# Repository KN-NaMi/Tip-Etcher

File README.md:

# 🧪 Tip Etcher for Scanning Tunneling Microscopy (STM) 🧪

**Overview**
This project is a **Tip Etcher** designed for the fabrication of fine tungsten tips required for **Scanning Tunneling Microscopy (STM)**. The inspiration for this project comes from the [Zyrus Tip Etcher](https://hackaday.io/project/191941-zyrus-tip-etcher-for-scanning-tunneling-microscopy) project, with modifications to improve performance and usability.

**✨ Proposed Changes ✨**
* Updated README.md
* Changed structure to vertical based desgin, using avaible aluminium profiles.
* Upgraded documentation in cad's folder
* Removed previous version's files in cad's folder

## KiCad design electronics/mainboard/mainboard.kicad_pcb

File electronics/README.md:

# PCB Design

This folder contains the PCB design files for the Tip Etcher.

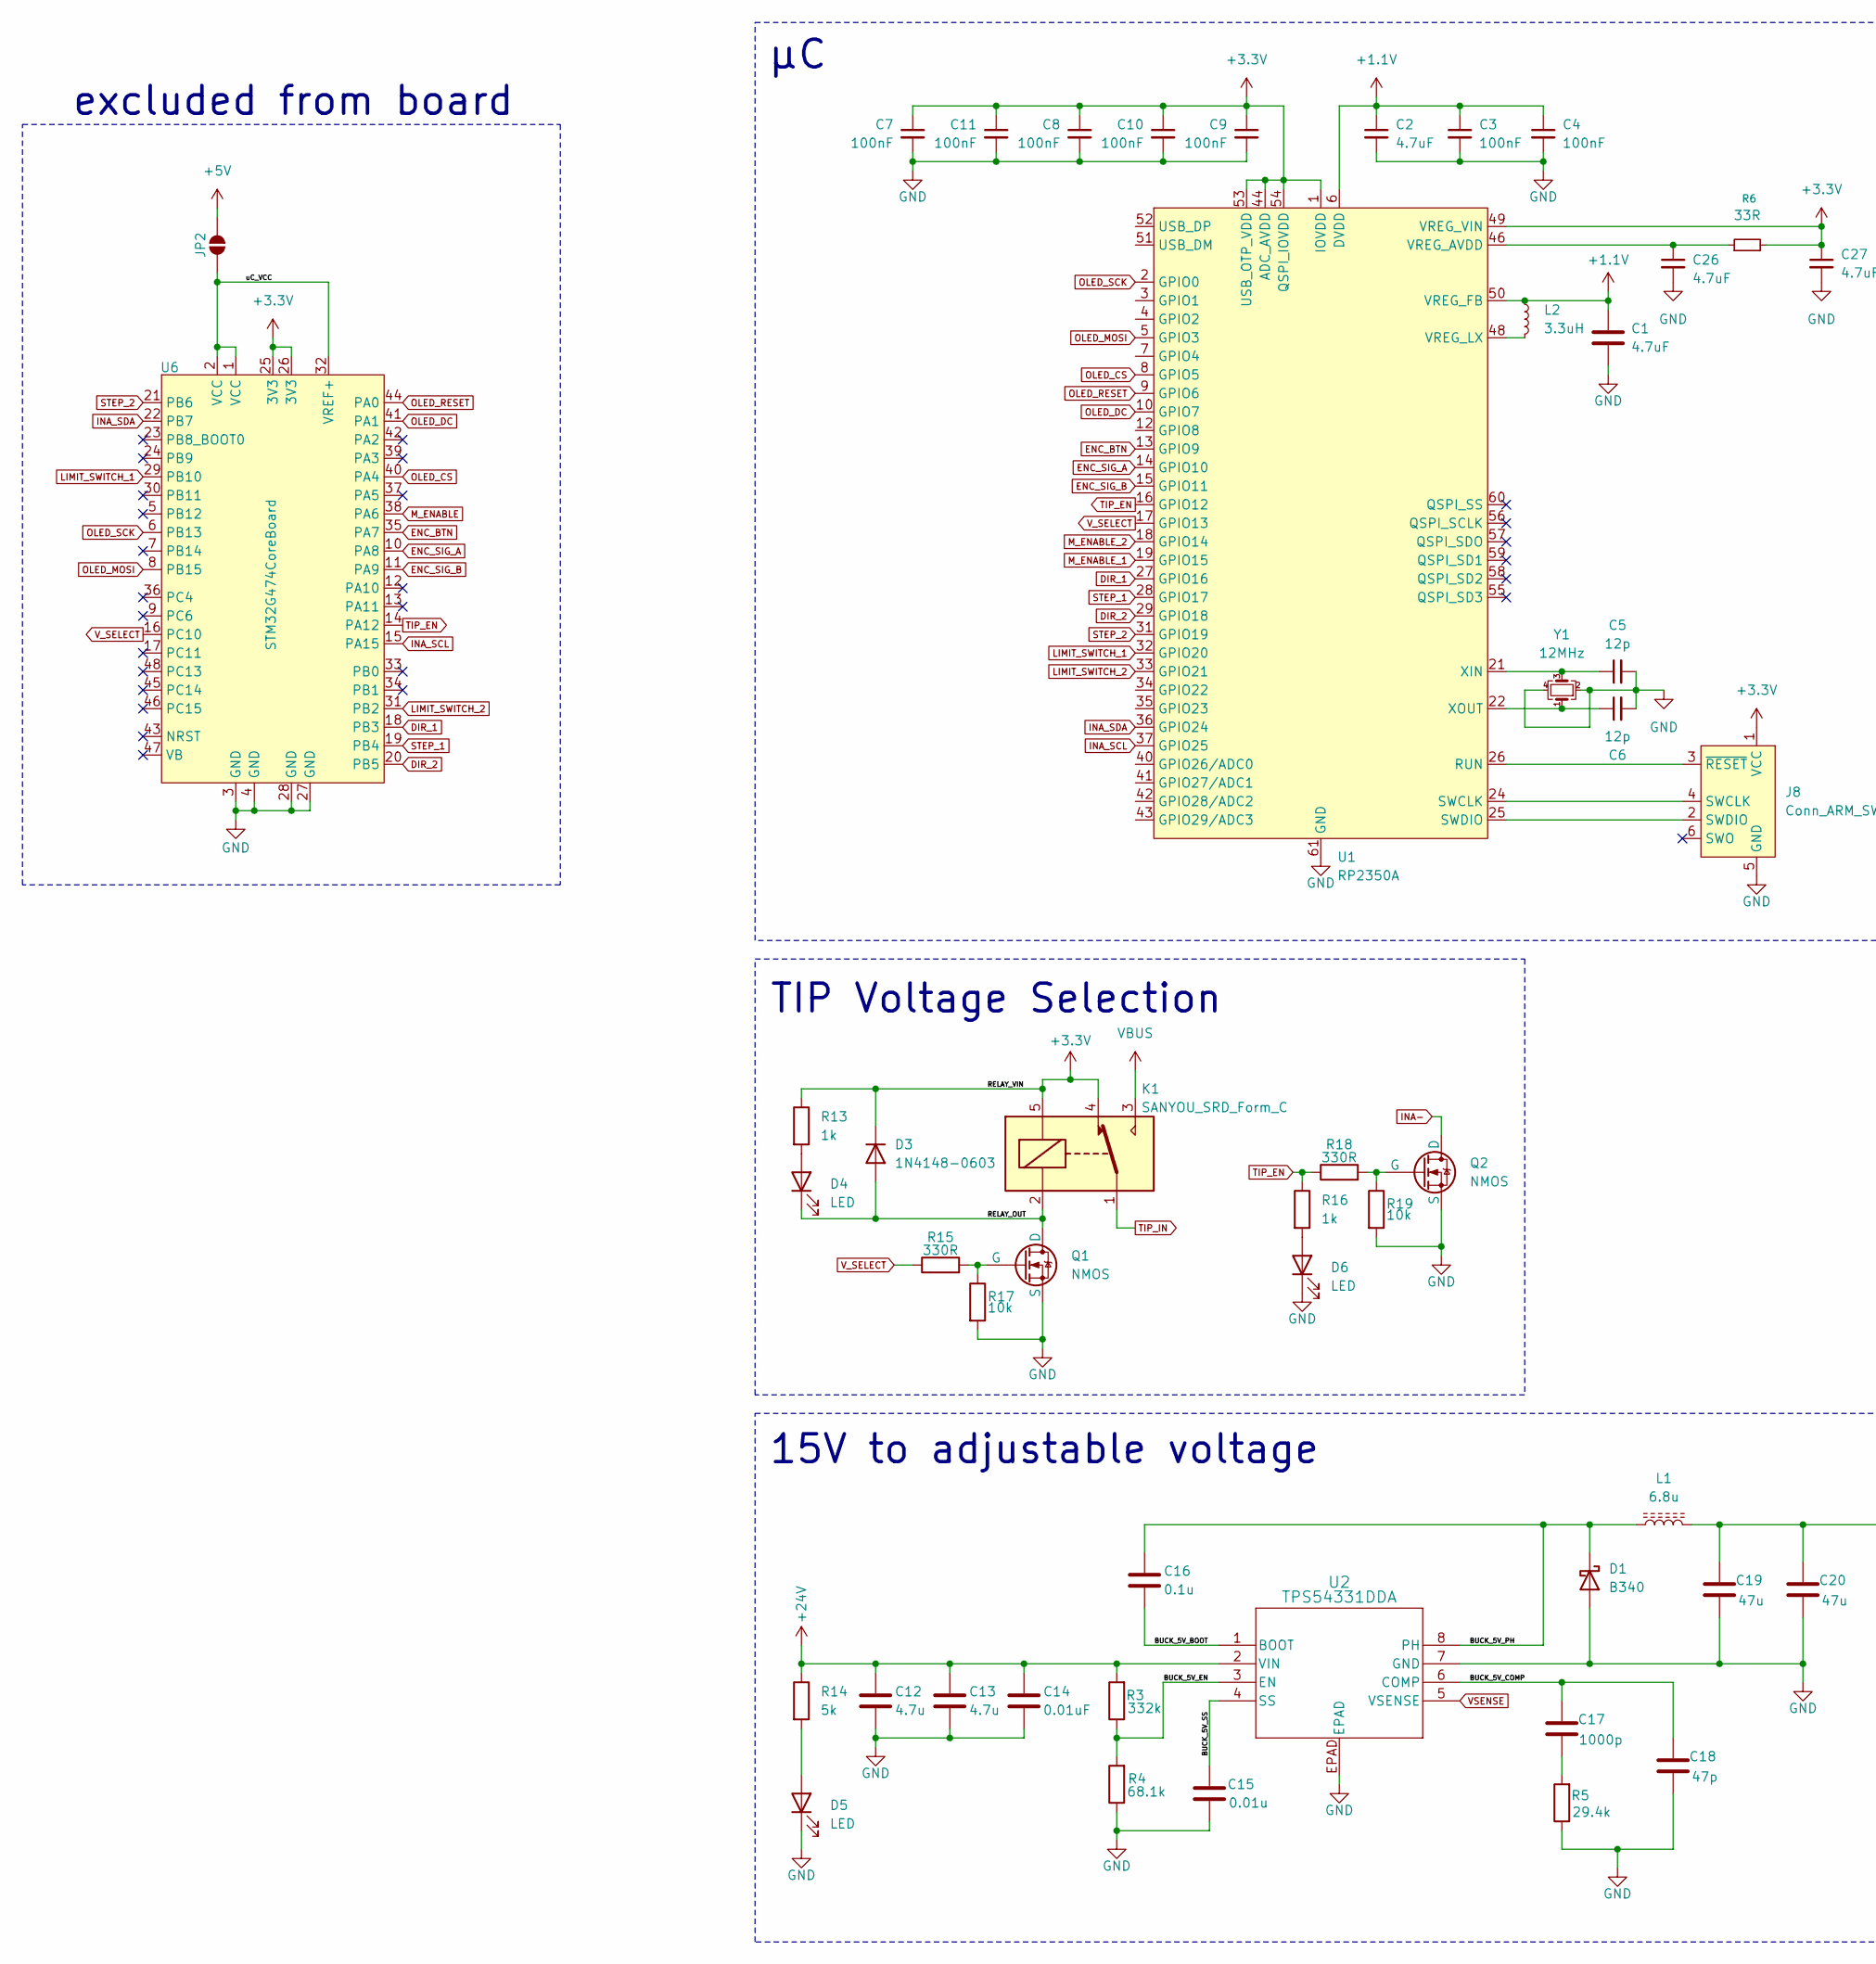
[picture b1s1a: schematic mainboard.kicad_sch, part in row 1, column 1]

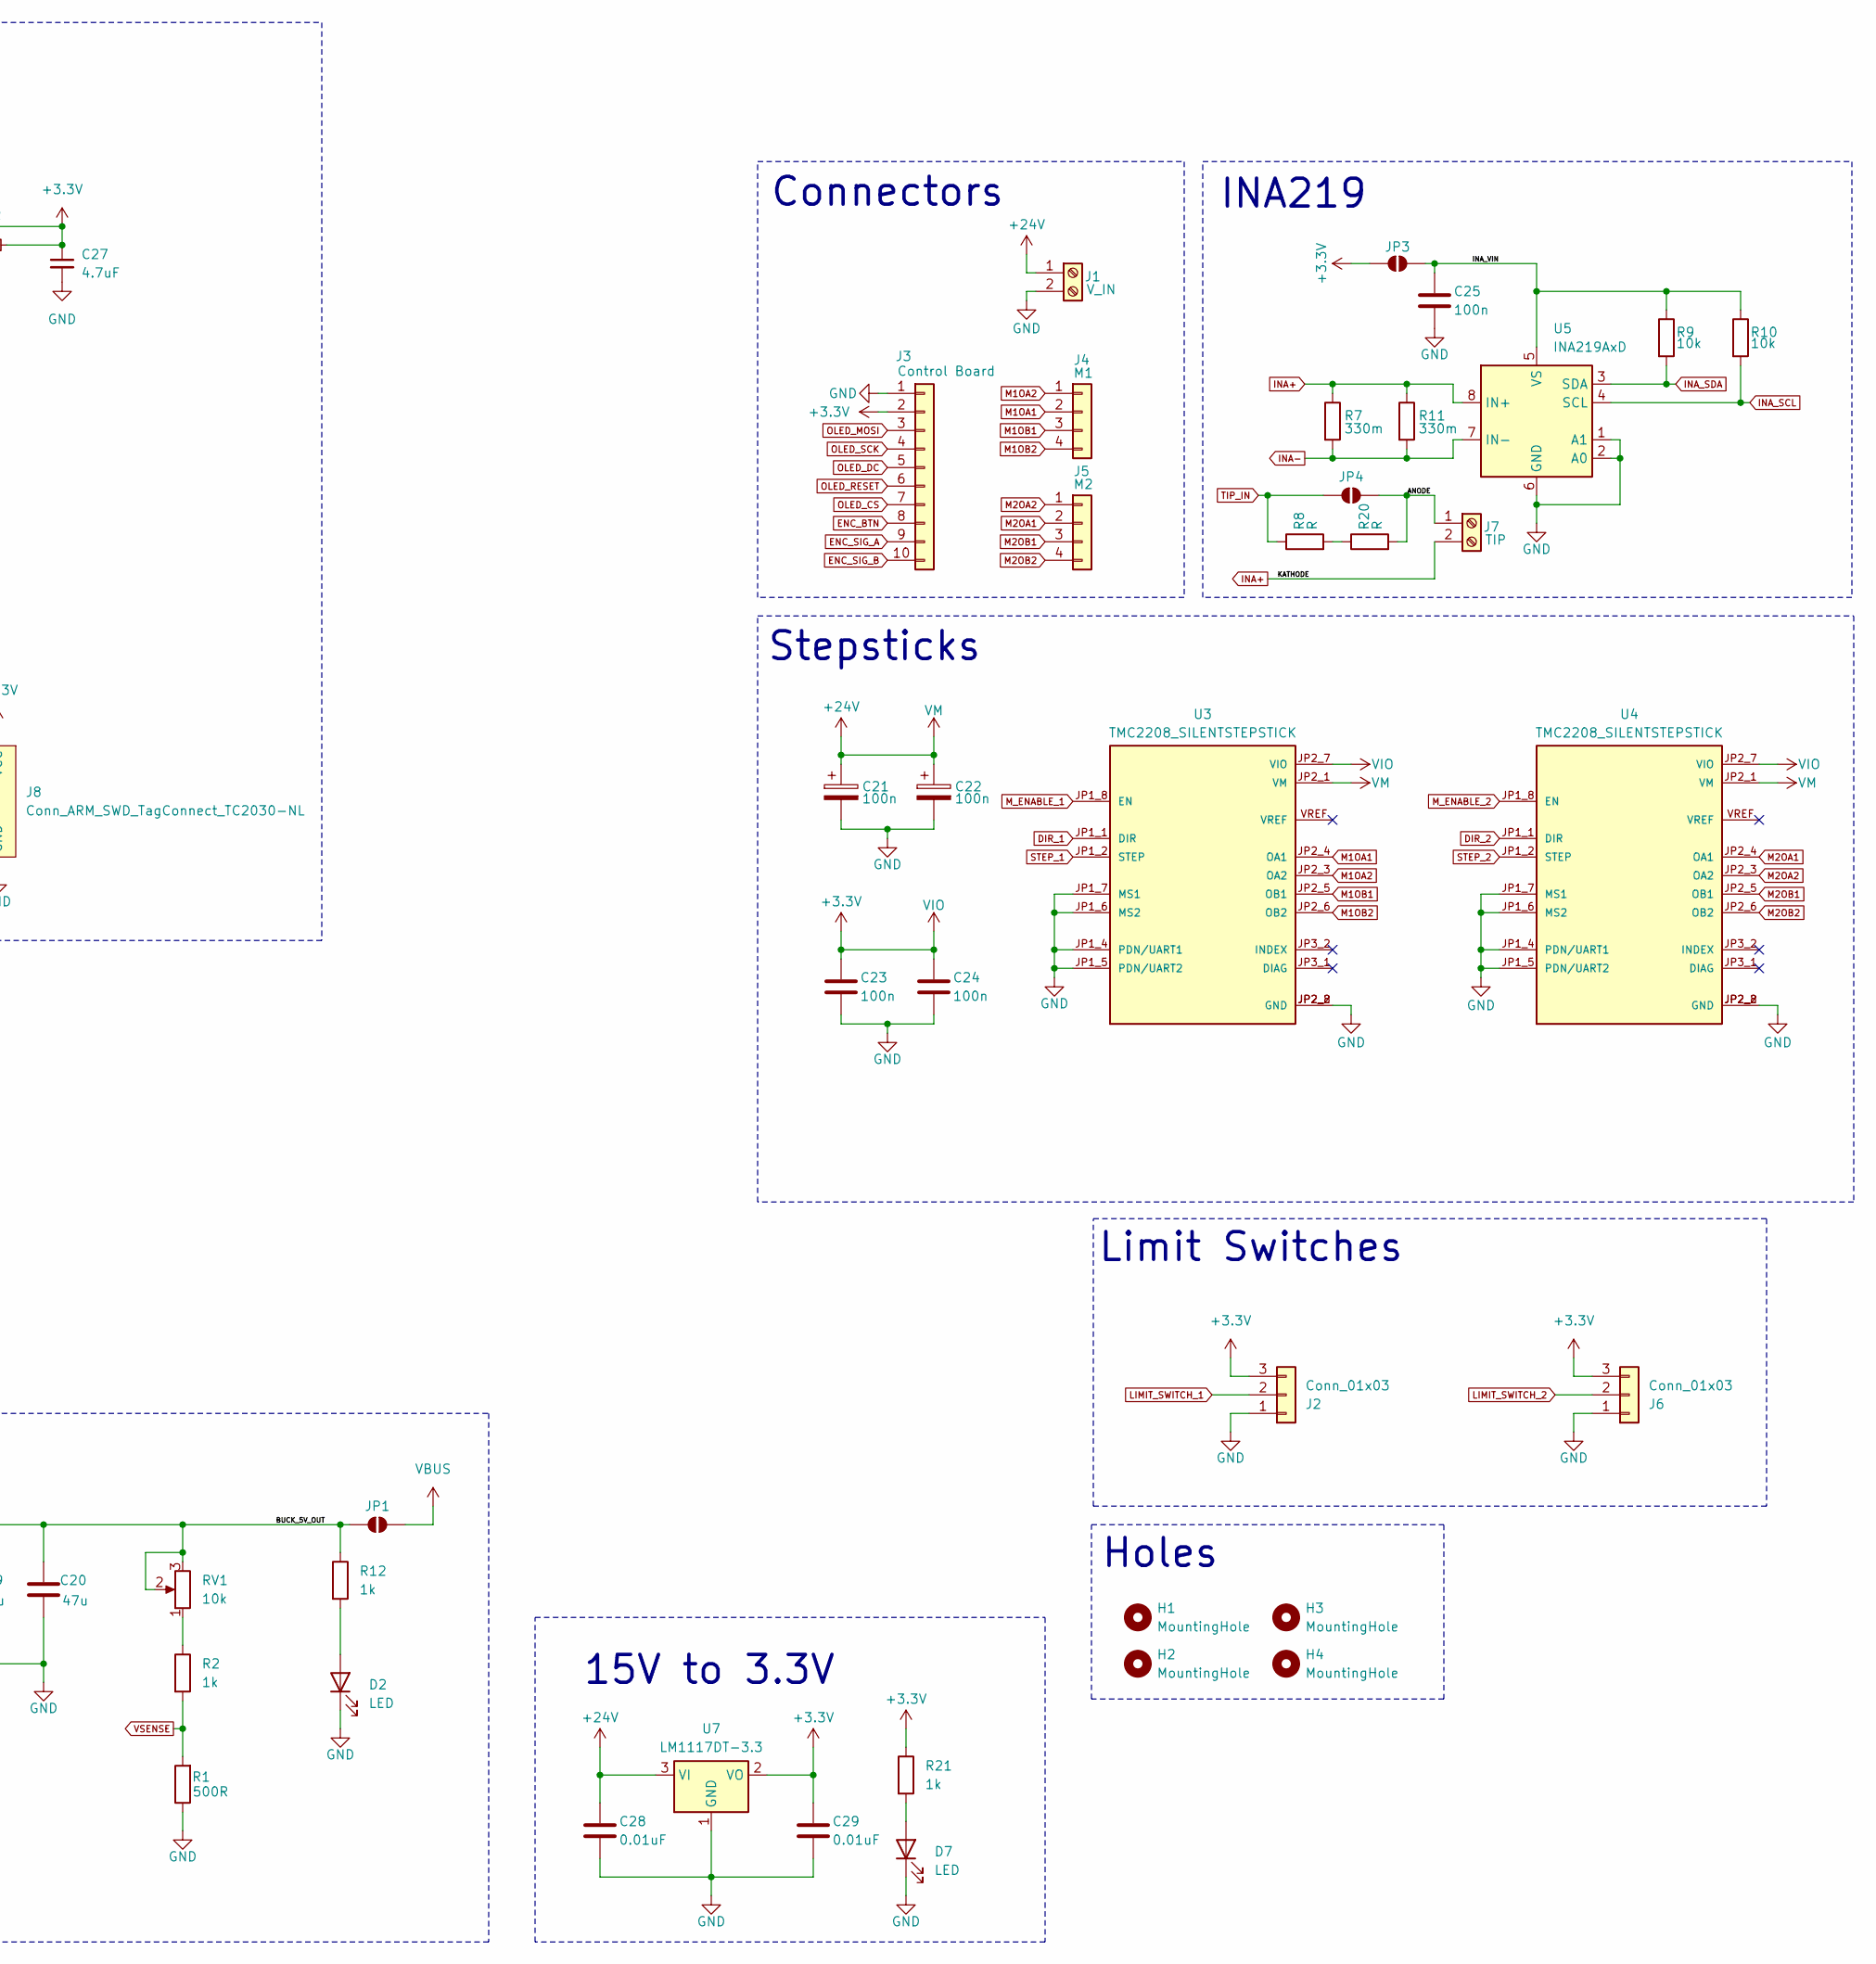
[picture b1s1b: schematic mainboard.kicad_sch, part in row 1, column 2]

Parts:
C1, C2, C26, C27: 4.7uF; C_0805_2012Metric_Pad1.18x1.45mm_HandSolder
C3, C4, C7, C8, C9, C10, C11: 100nF; C_0805_2012Metric_Pad1.18x1.45mm_HandSolder
C5, C6: 12p; C_0805_2012Metric_Pad1.18x1.45mm_HandSolder
C12, C13: 4.7u; C_0603_1608Metric_Pad1.08x0.95mm_HandSolder
C14, C28, C29: 0.01uF; C_0603_1608Metric_Pad1.08x0.95mm_HandSolder
C15: 0.01u; C_0603_1608Metric_Pad1.08x0.95mm_HandSolder
C16: 0.1u; C_0603_1608Metric_Pad1.08x0.95mm_HandSolder
C17: 1000p; C_0603_1608Metric_Pad1.08x0.95mm_HandSolder
C18: 47p; C_0603_1608Metric_Pad1.08x0.95mm_HandSolder
C19, C20: 47u; C_0603_1608Metric_Pad1.08x0.95mm_HandSolder
C21, C22: 100n; CP_Elec_6.3x7.7
C23, C24, C25: 100n; C_0603_1608Metric_Pad1.08x0.95mm_HandSolder
D1: B340; D_SMC
D2, D4, D5, D6, D7: LED; LED_0603_1608Metric_Pad1.05x0.95mm_HandSolder
D3: 1N4148-0603; D_1206_3216Metric
H1, H2, H3, H4: MountingHole; MountingHole_3.2mm_M3
J1: V_IN; CONN_395011002_MOL
J2, J6: Conn_01x03; PinSocket_1x03_P2.54mm_Vertical
J3: Control Board; PinSocket_1x10_P2.00mm_Vertical
J4: M1; PinSocket_1x04_P2.54mm_Vertical
J5: M2; PinSocket_1x04_P2.54mm_Vertical
J7: TIP; CONN_395011002_MOL
J8: Conn_ARM_SWD_TagConnect_TC2030-NL; Tag-Connect_TC2030-IDC-NL_2x03_P1.27mm_Vertical
JP1, JP2, JP3, JP4: SolderJumper_2_Open; SolderJumper-2_P1.3mm_Open_TrianglePad1.0x1.5mm
K1: SANYOU_SRD_Form_C; Relay_SPDT_SANYOU_SRD_Series_Form_C
L1: 6.8u; IND_IHLP-2525CZ_VIS-M
L2: 3.3uH; L_Neosid_SMs42
Q1, Q2: NMOS; SOT-23_Handsoldering
R1: 500R; R_0603_1608Metric_Pad0.98x0.95mm_HandSolder
R2, R12, R13, R16, R21: 1k; R_0603_1608Metric_Pad0.98x0.95mm_HandSolder
R3: 332k; R_0603_1608Metric_Pad0.98x0.95mm_HandSolder
R4: 68.1k; R_0603_1608Metric_Pad0.98x0.95mm_HandSolder
R5: 29.4k; R_0603_1608Metric_Pad0.98x0.95mm_HandSolder
R6: 33R; R_0805_2012Metric_Pad1.20x1.40mm_HandSolder
R7, R11: 330m; D_2512_6332Metric_Pad1.52x3.35mm_HandSolder
R8, R20: R; D_2512_6332Metric_Pad1.52x3.35mm_HandSolder
R9, R10, R17, R19: 10k; R_0603_1608Metric_Pad0.98x0.95mm_HandSolder
R14: 5k; R_0603_1608Metric_Pad0.98x0.95mm_HandSolder
R15, R18: 330R; R_0603_1608Metric_Pad0.98x0.95mm_HandSolder
RV1: 10k; Potentiometer_Vishay_T93YA_Vertical
U1: RP2350A; QFN-60-1EP_7x7mm_P0.4mm_EP3.4x3.4mm_ThermalVias
U2: TPS54331DDA; DDA8_3X2P13
U3, U4: TMC2208_SILENTSTEPSTICK; MODULE_TMC2208_SILENTSTEPSTICK
U5: INA219AxD; SOIC-8_3.9x4.9mm_P1.27mm
U6: STM32G474CoreBoard
U7: LM1117DT-3.3; SOT-223-3_TabPin2
Y1: 12MHz; Crystal_SMD_Abracon_ABM8AIG-4Pin_3.2x2.5mm

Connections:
+1.1V: C1.1, C2.1, C3.1, C4.1, L2.1, U1.6 (DVDD), U1.23 (DVDD), U1.39 (DVDD), U1.50 (VREG_FB)
+3.3V: C7.1, C8.1, C9.1, C10.1, C11.1, C23.1, C24.1, C27.1, C29.1, D3.1 (K), J2.3, J3.2, J6.3, J8.1 (VCC), JP3.1 (A), K1.4, K1.5, R6.2, R13.1, R21.1, U1.1 (IOVDD), U1.11 (IOVDD), U1.20 (IOVDD), U1.30 (IOVDD), U1.38 (IOVDD), U1.44 (ADC_AVDD), U1.45 (IOVDD), U1.49 (VREG_VIN), U1.53 (USB_OTP_VDD), U1.54 (QSPI_IOVDD), U3.JP2_7 (VIO), U4.JP2_7 (VIO), U6.25 (3V3), U6.26 (3V3), U7.2 (VO)
+24V: C12.1, C13.1, C14.1, C21.1, C22.1, C28.1, J1.1, R3.2, R14.1, U2.2 (VIN), U3.JP2_1 (VM), U4.JP2_1 (VM), U7.3 (VI)
/ANODE: J7.1, JP4.2 (B), R20.2
/BUCK_5V_BOOT: C16.2, U2.1 (BOOT)
/BUCK_5V_COMP: C17.1, C18.1, U2.6 (COMP)
/BUCK_5V_EN: R3.1, R4.2, U2.3 (EN)
/BUCK_5V_PH: C16.1, D1.1 (K), L1.1, U2.8 (PH)
/BUCK_5V_SS: C15.1, U2.4 (SS)
/INA_VIN: C25.1, JP3.2 (B), R9.1, R10.1, U5.5 (VS)
/RELAY_OUT: D3.2 (A), D4.1 (K), K1.2, Q1.3 (D)
DIR_1: U1.27 (GPIO16), U3.JP1_1 (DIR), U6.18 (PB3)
DIR_2: U1.29 (GPIO18), U4.JP1_1 (DIR), U6.20 (PB5)
ENC_BTN: J3.8, U1.13 (GPIO9), U6.35 (PA7)
ENC_SIG_A: J3.9, U1.14 (GPIO10), U6.10 (PA8)
ENC_SIG_B: J3.10, U1.15 (GPIO11), U6.11 (PA9)
GND: C1.2, C2.2, C3.2, C4.2, C5.2, C6.2, C7.2, C8.2, C9.2, C10.2, C11.2, C12.2, C13.2, C14.2, C15.2, C18.2, C19.2, C20.2, C21.2, C22.2, C23.2, C24.2, C25.2, C26.2, C27.2, C28.2, C29.2, D1.2 (A), D2.1 (K), D5.1 (K), D6.1 (K), D7.1 (K), J1.2, J2.1, J3.1, J6.1, J8.5 (GND), Q1.2 (S), Q2.2 (S), R1.1, R4.1, R5.1, R17.2, R19.2, U1.47 (VREG_PGND), U1.61 (GND), U2.7 (GND), U2.EPAD, U3.JP1_4 (PDN/UART1), U3.JP1_5 (PDN/UART2), U3.JP1_6 (MS2), U3.JP1_7 (MS1), U3.JP2_2 (GND), U3.JP2_8 (GND), U4.JP1_4 (PDN/UART1), U4.JP1_5 (PDN/UART2), U4.JP1_6 (MS2), U4.JP1_7 (MS1), U4.JP2_2 (GND), U4.JP2_8 (GND), U5.1 (A1), U5.2 (A0), U5.6 (GND), U6.3 (GND), U6.4 (GND), U6.27 (GND), U6.28 (GND), U7.1 (GND), Y1.2, Y1.4; also elsewhere on the board
INA_SCL: R10.2, U1.37 (GPIO25), U5.4 (SCL), U6.15 (PA15)
INA_SDA: R9.2, U1.36 (GPIO24), U5.3 (SDA), U6.22 (PB7)
LIMIT_SWITCH_1: J2.2, U1.32 (GPIO20), U6.29 (PB10)
LIMIT_SWITCH_2: J6.2, U1.33 (GPIO21), U6.31 (PB2)
M1OA1: J4.2, U3.JP2_4 (OA1)
M1OA2: J4.1, U3.JP2_3 (OA2)
M1OB1: J4.3, U3.JP2_5 (OB1)
M1OB2: J4.4, U3.JP2_6 (OB2)
M2OA1: J5.2, U4.JP2_4 (OA1)
M2OA2: J5.1, U4.JP2_3 (OA2)
M2OB1: J5.3, U4.JP2_5 (OB1)
M2OB2: J5.4, U4.JP2_6 (OB2)
M_ENABLE_1: U1.19 (GPIO15), U3.JP1_8 (EN)
M_ENABLE_2: U1.18 (GPIO14), U4.JP1_8 (EN)
unnamed: C17.2, R5.2
unnamed: D2.2 (A), R12.2
unnamed: D4.2 (A), R13.2
unnamed: D5.2 (A), R14.2
unnamed: D6.2 (A), R16.2
unnamed: D7.2 (A), R21.2
unnamed: J8.4 (SWCLK), U1.24 (SWCLK)
unnamed: J8.2 (SWDIO), U1.25 (SWDIO)
unnamed: J8.3 (~RESET), U1.26 (RUN)
unnamed: JP2.2 (B), U6.1 (VCC), U6.2 (VCC), U6.32 (VREF+)
unnamed: Q1.1 (G), R15.2, R17.1
unnamed: Q2.1 (G), R18.2, R19.1
unnamed: R2.1, RV1.1
unnamed: R8.2, R20.1
unnamed: C26.1, R6.1, U1.46 (VREG_AVDD)
unnamed: L2.2, U1.48 (VREG_LX)
unnamed: C5.1, U1.21 (XIN), Y1.3
unnamed: C6.1, U1.22 (XOUT), Y1.1
OLED_CS: J3.7, U1.8 (GPIO5), U6.40 (PA4)
OLED_DC: J3.5, U1.10 (GPIO7), U6.41 (PA1)
OLED_MOSI: J3.3, U1.5 (GPIO3), U6.8 (PB15)
OLED_RESET: J3.6, U1.9 (GPIO6), U6.44 (PA0)
OLED_SCK: J3.4, U1.2 (GPIO0), U6.6 (PB13)
STEP_1: U1.28 (GPIO17), U3.JP1_2 (STEP), U6.19 (PB4)
STEP_2: U1.31 (GPIO19), U4.JP1_2 (STEP), U6.21 (PB6)
TIP_EN: R16.1, R18.1, U1.16 (GPIO12), U6.14 (PA12)
TIP_IN: JP4.1 (A), K1.1, R8.1
VBUS: JP1.2 (B), K1.3
V_SELECT: R15.1, U1.17 (GPIO13), U6.16 (PC10)

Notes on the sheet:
Connectors
excluded from board
TIP Voltage Selection
15V to adjustable voltage
Limit Switches
INA219
15V to 3.3V
Stepsticks
Holes

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
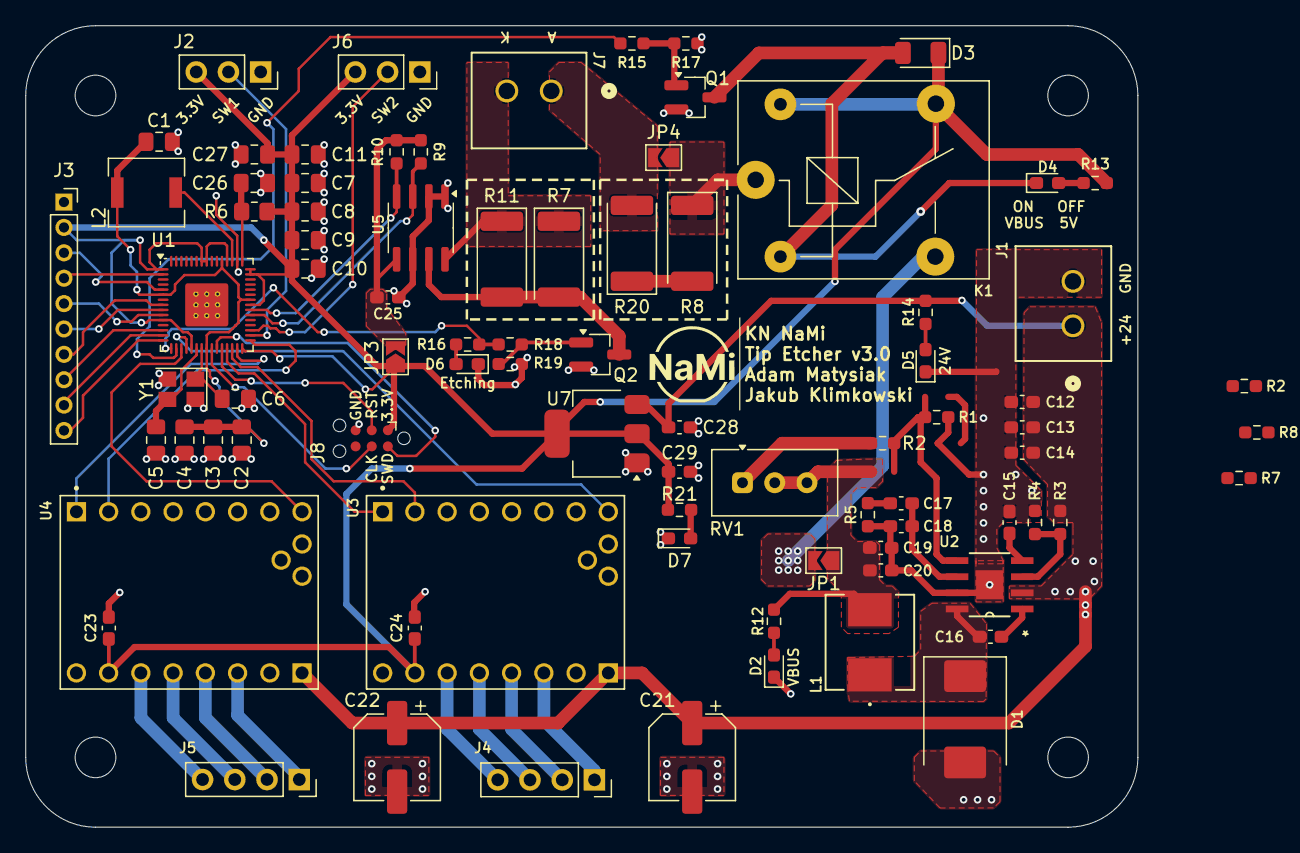
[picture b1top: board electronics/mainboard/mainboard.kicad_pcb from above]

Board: 2 copper layers, 87.6 x 63.1 mm, 88 parts (0 on the bottom side), 64 nets.

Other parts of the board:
R2#2, R8#2: 1k; R_0603_1608Metric_Pad0.98x0.95mm_HandSolder
R7#2: 330m; D_2512_6332Metric_Pad1.52x3.35mm_HandSolder

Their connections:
GND: R8#2.1; also elsewhere on the board
unnamed: R2#2.1, R8#2.2

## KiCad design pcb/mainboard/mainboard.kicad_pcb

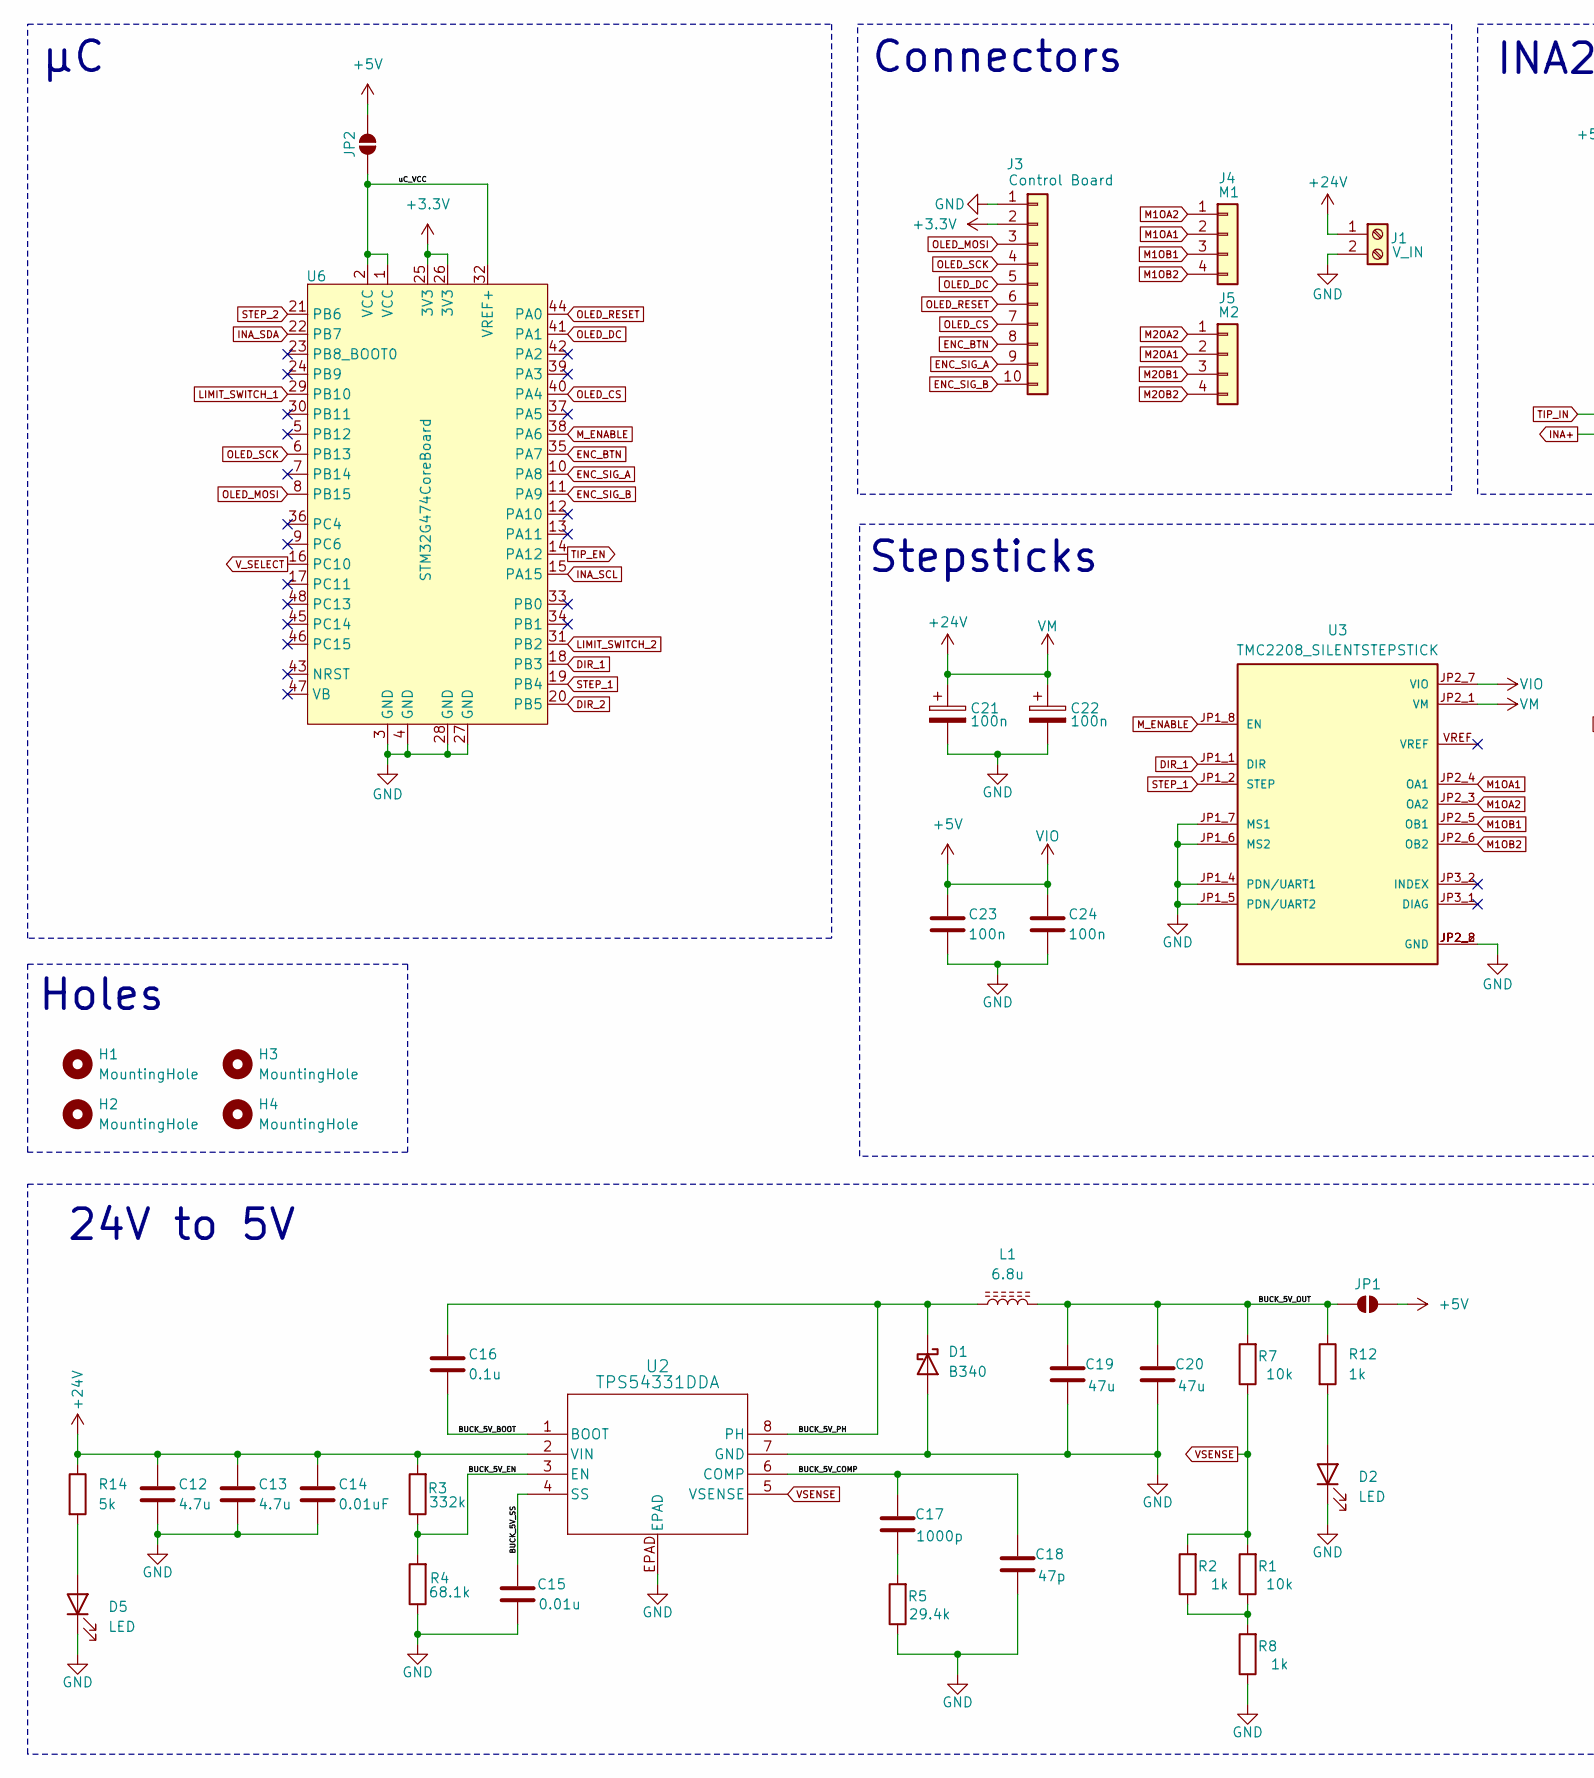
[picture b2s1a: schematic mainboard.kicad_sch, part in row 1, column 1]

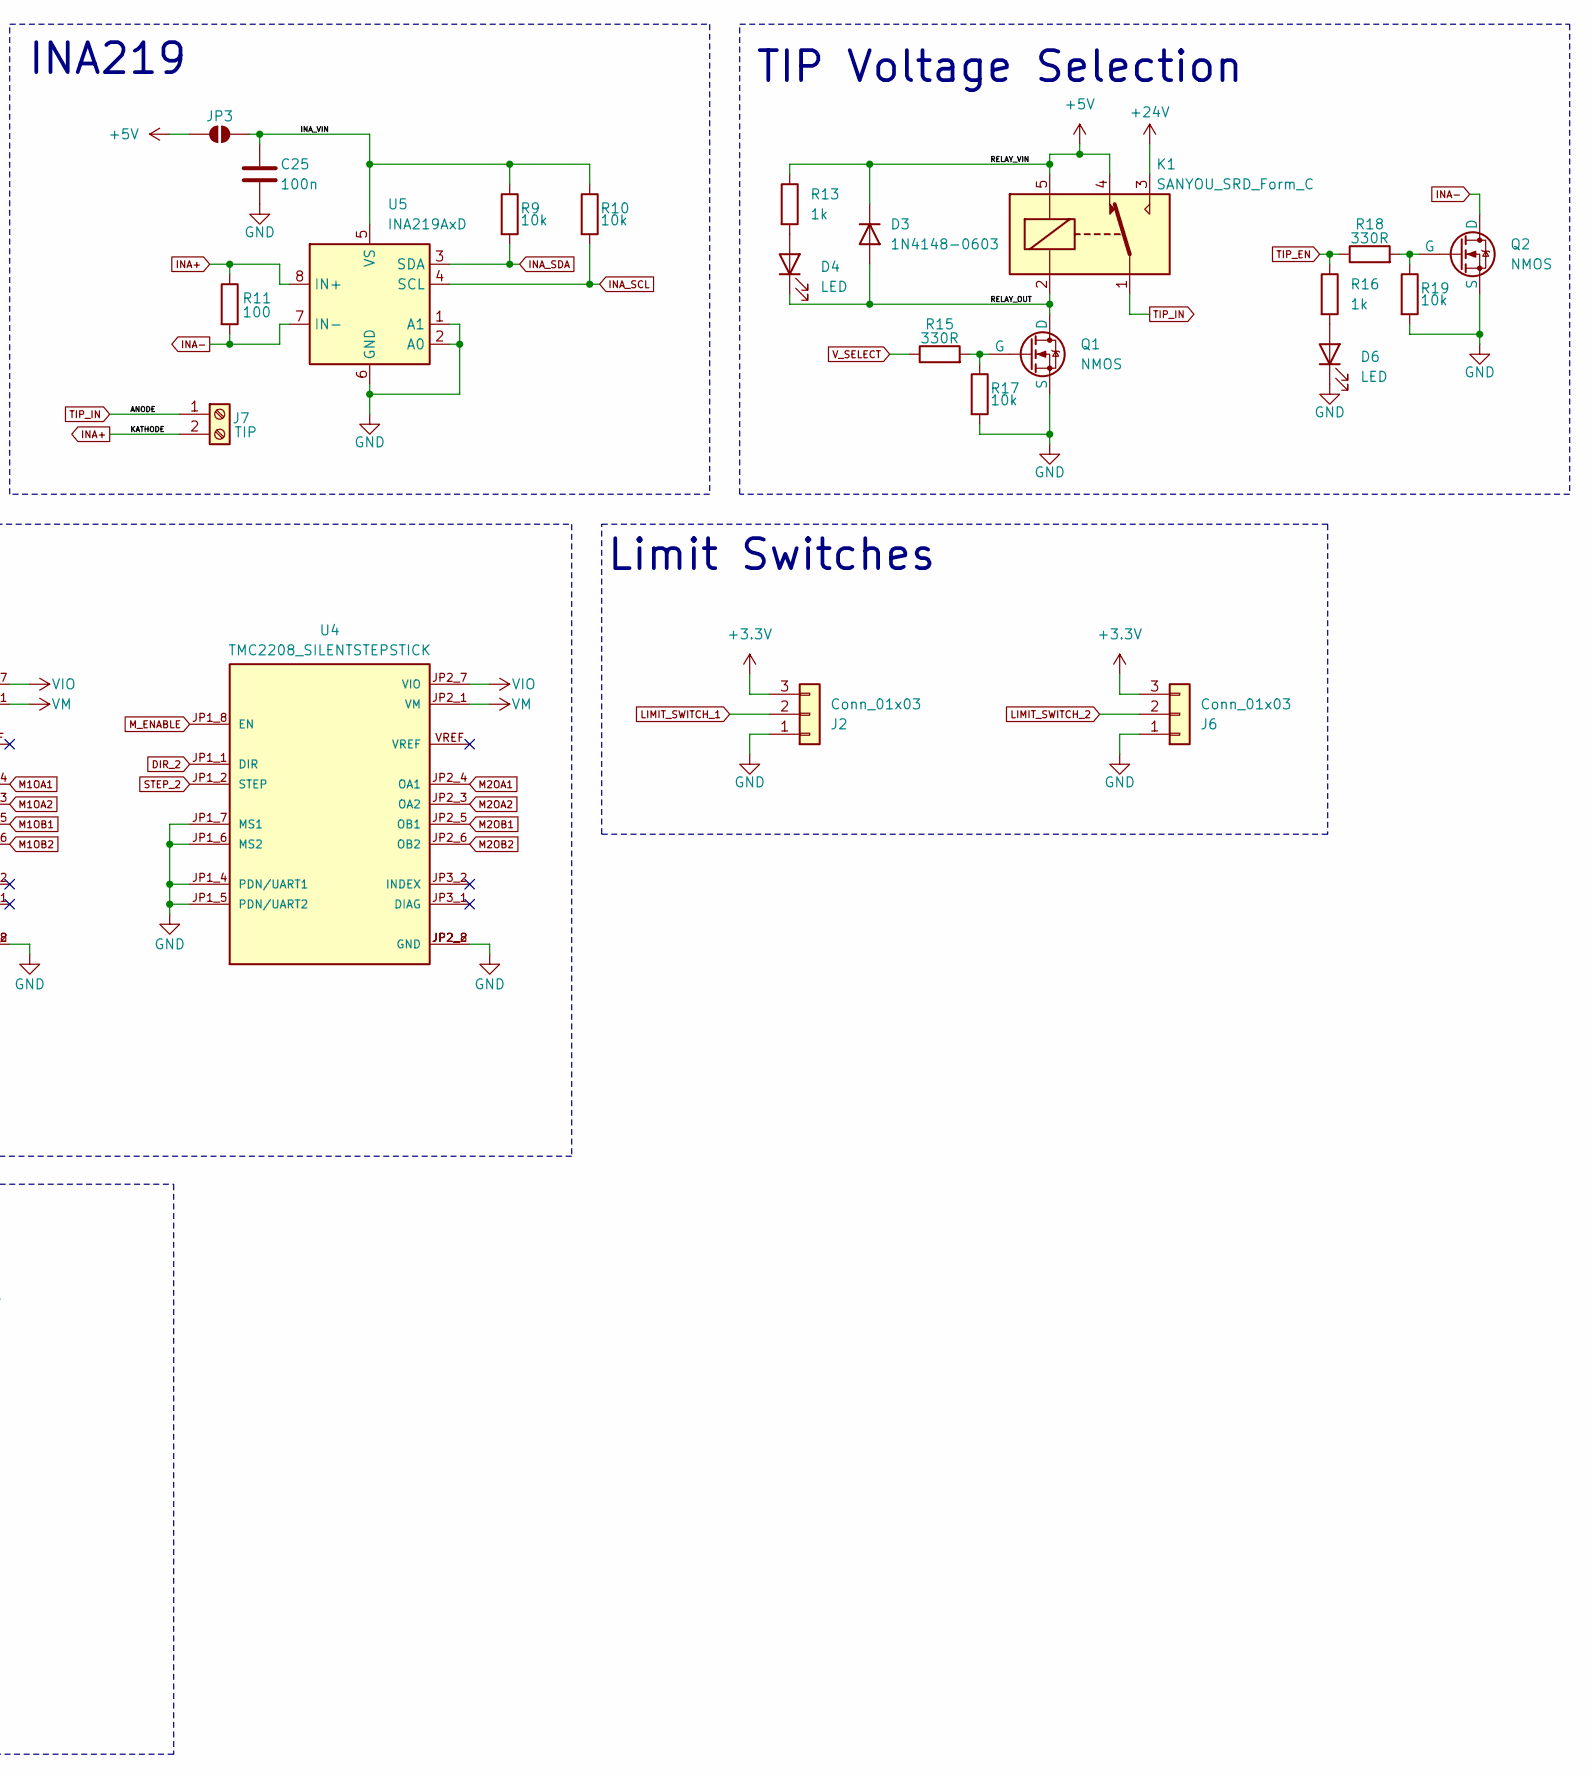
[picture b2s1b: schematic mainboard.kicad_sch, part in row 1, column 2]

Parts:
C12, C13: 4.7u; C_0603_1608Metric_Pad1.08x0.95mm_HandSolder
C14: 0.01uF; C_0603_1608Metric_Pad1.08x0.95mm_HandSolder
C15: 0.01u; C_0603_1608Metric_Pad1.08x0.95mm_HandSolder
C16: 0.1u; C_0603_1608Metric_Pad1.08x0.95mm_HandSolder
C17: 1000p; C_0603_1608Metric_Pad1.08x0.95mm_HandSolder
C18: 47p; C_0603_1608Metric_Pad1.08x0.95mm_HandSolder
C19, C20: 47u; C_0603_1608Metric_Pad1.08x0.95mm_HandSolder
C21, C22: 100n; CP_Elec_4x4.5
C23, C24, C25: 100n; C_0603_1608Metric_Pad1.08x0.95mm_HandSolder
D1: B340; D_SMC
D2, D4, D5, D6: LED; LED_0603_1608Metric_Pad1.05x0.95mm_HandSolder
D3: 1N4148-0603; D_0603_1608Metric_Pad1.05x0.95mm_HandSolder
H1, H2, H3, H4: MountingHole; MountingHole_3.2mm_M3
J1: V_IN; CONN_395011002_MOL
J2, J6: Conn_01x03; PinSocket_1x03_P2.54mm_Vertical
J3: Control Board; PinSocket_1x10_P2.00mm_Vertical
J4: M1; PinSocket_1x04_P2.54mm_Vertical
J5: M2; PinSocket_1x04_P2.54mm_Vertical
J7: TIP; CONN_395011002_MOL
JP1, JP2, JP3: SolderJumper_2_Open; SolderJumper-2_P1.3mm_Open_TrianglePad1.0x1.5mm
K1: SANYOU_SRD_Form_C; Relay_SPDT_SANYOU_SRD_Series_Form_C
L1: 6.8u; IND_IHLP-2525CZ_VIS-M
Q1, Q2: NMOS; SOT-23_Handsoldering
R1, R7, R9, R10, R17, R19: 10k; R_0603_1608Metric_Pad0.98x0.95mm_HandSolder
R2, R8, R12, R13, R16: 1k; R_0603_1608Metric_Pad0.98x0.95mm_HandSolder
R3: 332k; R_0603_1608Metric_Pad0.98x0.95mm_HandSolder
R4: 68.1k; R_0603_1608Metric_Pad0.98x0.95mm_HandSolder
R5: 29.4k; R_0603_1608Metric_Pad0.98x0.95mm_HandSolder
R11: 100; R_1206_3216Metric_Pad1.30x1.75mm_HandSolder
R14: 5k; R_0603_1608Metric_Pad0.98x0.95mm_HandSolder
R15, R18: 330R; R_0603_1608Metric_Pad0.98x0.95mm_HandSolder
U2: TPS54331DDA; DDA8_3X2P13
U3, U4: TMC2208_SILENTSTEPSTICK; MODULE_TMC2208_SILENTSTEPSTICK
U5: INA219AxD; SOIC-8_3.9x4.9mm_P1.27mm
U6: STM32G474CoreBoard

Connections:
+3.3V: J2.3, J3.2, J6.3, U6.25 (3V3), U6.26 (3V3)
+5V: C23.1, C24.1, D3.1 (K), JP1.2 (B), JP2.1 (A), JP3.1 (A), K1.4, K1.5, R13.1, U3.JP2_7 (VIO), U4.JP2_7 (VIO)
+24V: C12.1, C13.1, C14.1, C21.1, C22.1, J1.1, K1.3, R3.2, R14.1, U2.2 (VIN), U3.JP2_1 (VM), U4.JP2_1 (VM)
/BUCK_5V_BOOT: C16.2, U2.1 (BOOT)
/BUCK_5V_COMP: C17.1, C18.1, U2.6 (COMP)
/BUCK_5V_EN: R3.1, R4.2, U2.3 (EN)
/BUCK_5V_OUT: C19.1, C20.1, JP1.1 (A), L1.2, R7.2, R12.1
/BUCK_5V_PH: C16.1, D1.1 (K), L1.1, U2.8 (PH)
/BUCK_5V_SS: C15.1, U2.4 (SS)
/INA_VIN: C25.1, JP3.2 (B), R9.1, R10.1, U5.5 (VS)
/RELAY_OUT: D3.2 (A), D4.1 (K), K1.2, Q1.1 (D)
/uC_VCC: JP2.2 (B), U6.1 (VCC), U6.2 (VCC), U6.32 (VREF+)
DIR_1: U3.JP1_1 (DIR), U6.18 (PB3)
DIR_2: U4.JP1_1 (DIR), U6.20 (PB5)
ENC_BTN: J3.8, U6.35 (PA7)
ENC_SIG_A: J3.9, U6.10 (PA8)
ENC_SIG_B: J3.10, U6.11 (PA9)
GND: C12.2, C13.2, C14.2, C15.2, C18.2, C19.2, C20.2, C21.2, C22.2, C23.2, C24.2, C25.2, D1.2 (A), D2.1 (K), D5.1 (K), D6.1 (K), J1.2, J2.1, J3.1, J6.1, Q1.3 (S), Q2.3 (S), R4.1, R5.1, R8.1, R17.2, R19.2, U2.7 (GND), U2.EPAD, U3.JP1_4 (PDN/UART1), U3.JP1_5 (PDN/UART2), U3.JP1_6 (MS2), U3.JP1_7 (MS1), U3.JP2_2 (GND), U3.JP2_8 (GND), U4.JP1_4 (PDN/UART1), U4.JP1_5 (PDN/UART2), U4.JP1_6 (MS2), U4.JP1_7 (MS1), U4.JP2_2 (GND), U4.JP2_8 (GND), U5.1 (A1), U5.2 (A0), U5.6 (GND), U6.3 (GND), U6.4 (GND), U6.27 (GND), U6.28 (GND)
INA+: J7.2, R11.1, U5.8 (IN+)
INA-: Q2.1 (D), R11.2, U5.7 (IN-)
INA_SCL: R10.2, U5.4 (SCL), U6.15 (PA15)
INA_SDA: R9.2, U5.3 (SDA), U6.22 (PB7)
LIMIT_SWITCH_1: J2.2, U6.29 (PB10)
LIMIT_SWITCH_2: J6.2, U6.31 (PB2)
M1OA1: J4.2, U3.JP2_4 (OA1)
M1OA2: J4.1, U3.JP2_3 (OA2)
M1OB1: J4.3, U3.JP2_5 (OB1)
M1OB2: J4.4, U3.JP2_6 (OB2)
M2OA1: J5.2, U4.JP2_4 (OA1)
M2OA2: J5.1, U4.JP2_3 (OA2)
M2OB1: J5.3, U4.JP2_5 (OB1)
M2OB2: J5.4, U4.JP2_6 (OB2)
M_ENABLE: U3.JP1_8 (EN), U4.JP1_8 (EN), U6.38 (PA6)
unnamed: C17.2, R5.2
unnamed: D2.2 (A), R12.2
unnamed: D4.2 (A), R13.2
unnamed: D5.2 (A), R14.2
unnamed: D6.2 (A), R16.2
unnamed: Q1.2 (G), R15.2, R17.1
unnamed: Q2.2 (G), R18.2, R19.1
unnamed: R1.1, R2.1, R8.2
OLED_CS: J3.7, U6.40 (PA4)
OLED_DC: J3.5, U6.41 (PA1)
OLED_MOSI: J3.3, U6.8 (PB15)
OLED_RESET: J3.6, U6.44 (PA0)
OLED_SCK: J3.4, U6.6 (PB13)
STEP_1: U3.JP1_2 (STEP), U6.19 (PB4)
STEP_2: U4.JP1_2 (STEP), U6.21 (PB6)
TIP_EN: R16.1, R18.1, U6.14 (PA12)
TIP_IN: J7.1, K1.1
VSENSE: R1.2, R2.2, R7.1, U2.5 (VSENSE)
V_SELECT: R15.1, U6.16 (PC10)

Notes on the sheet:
Connectors
TIP Voltage Selection
24V to 5V
Limit Switches
INA219
Stepsticks
Holes
